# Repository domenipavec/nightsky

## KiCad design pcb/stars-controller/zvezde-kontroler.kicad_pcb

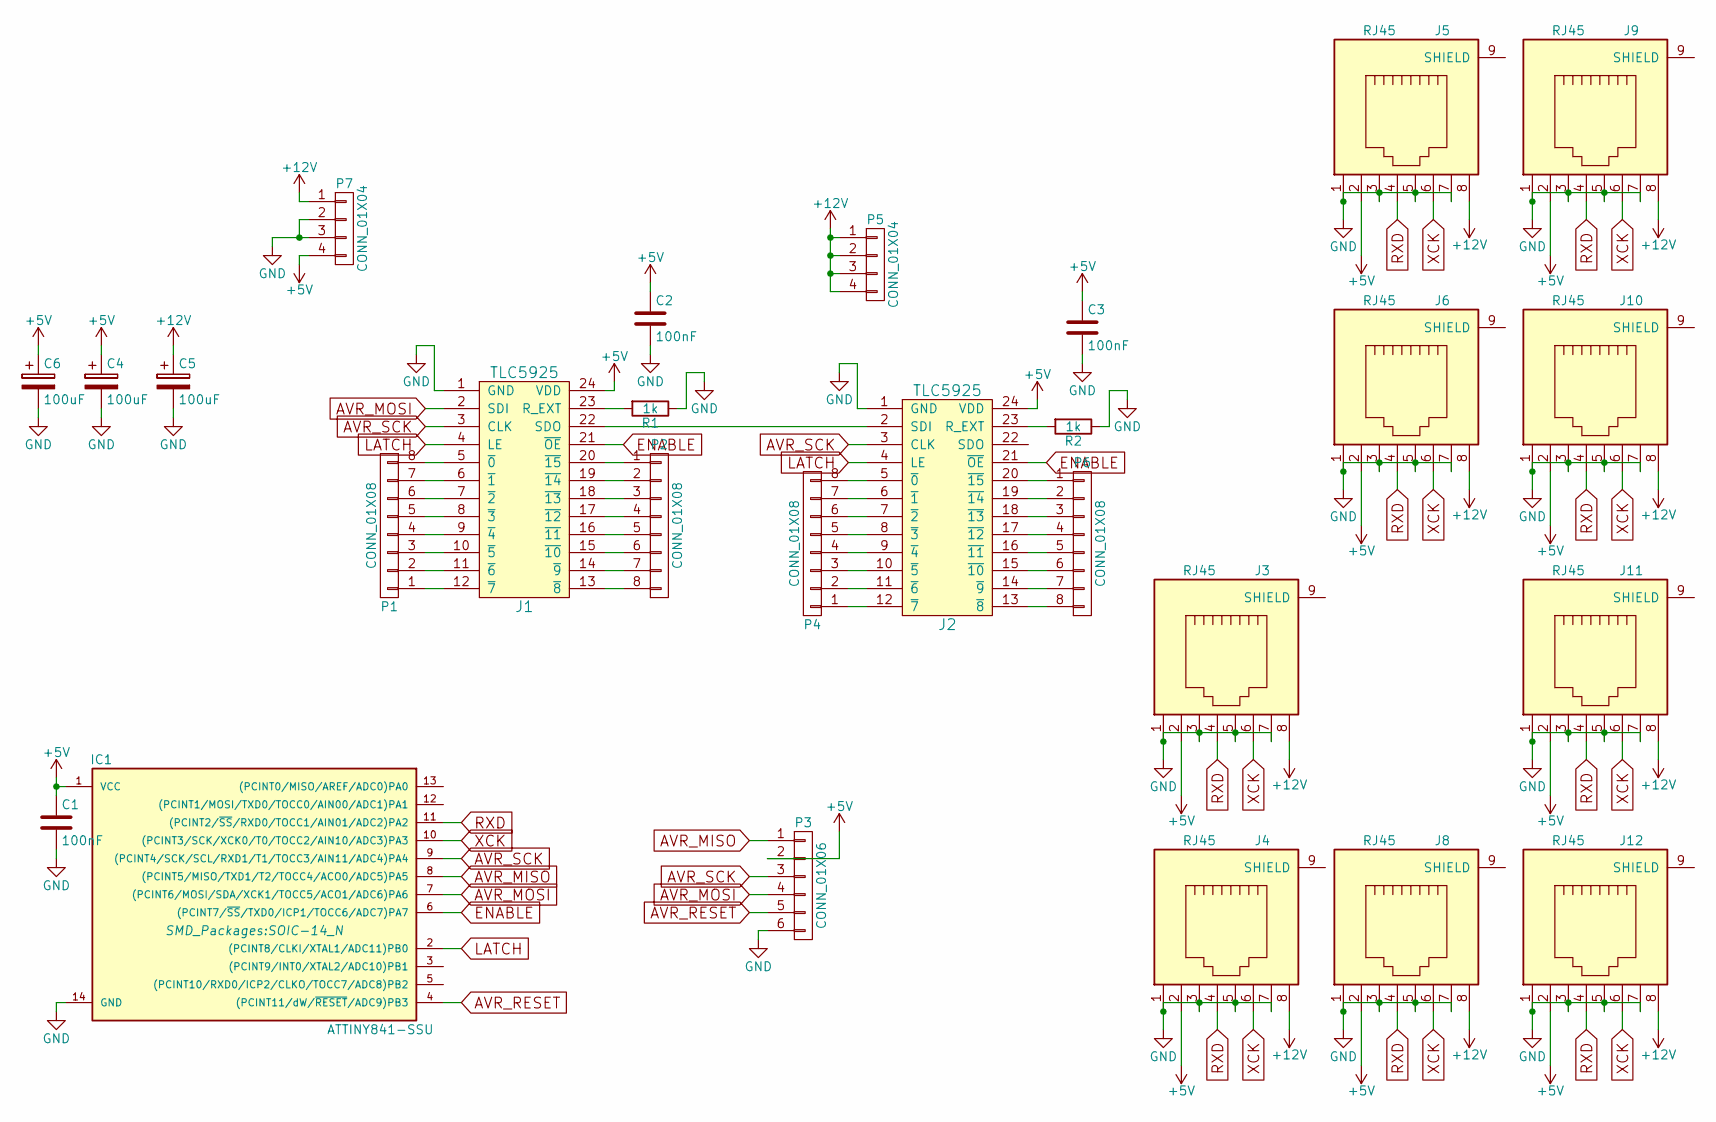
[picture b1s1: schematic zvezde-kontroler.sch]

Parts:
C1, C2, C3: 100nF; C_0603_HandSoldering
C4, C5, C6: 100uF; C_Radial_D6.3_L11.2_P2.5
IC1: ATTINY841-SSU; SOIC-14_N
J1, J2: TLC5925; SOIC-24W_7.5x15.4mm_Pitch1.27mm
J3, J4, J5, J6, J8, J9, J10, J11, J12: RJ45
P1, P2, P4, P6: CONN_01X08; Socket_Strip_Straight_1x08
P3: CONN_01X06; Pin_Header_Straight_2x03_Pitch2.54mm
P5: CONN_01X04; Socket_Strip_Straight_1x04
P7: CONN_01X04; molex
R1, R2: 1k; R_0805_HandSoldering

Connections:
+5V: C1.1, C2.1, C3.1, C4.1, C6.1, IC1.1 (VCC), J1.24 (VDD), J2.24 (VDD), J3.2, J4.2, J5.2, J6.2, J8.2, J9.2, J10.2, J11.2, J12.2, P3.2, P7.4
+12V: C5.1, J3.8, J4.8, J5.8, J6.8, J8.8, J9.8, J10.8, J11.8, J12.8, P5.1, P5.2, P5.3, P5.4, P7.1
AVR_MISO: IC1.8 ((PCINT5/MISO/TXD1/T2/TOCC4/ACO0/ADC5)PA5), P3.1
AVR_MOSI: IC1.7 ((PCINT6/MOSI/SDA/XCK1/TOCC5/ACO1/ADC6)P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), J1.2 (SDI), P3.4
AVR_RESET: IC1.4 ((PCINT11/dW/~RESET~/ADC9)PB3), P3.5
AVR_SCK: IC1.9 ((PCINT4/SCK/SCL/RXD1/T1/TOCC3/AIN11/ADC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), J1.3 (CLK), J2.3 (CLK), P3.3
ENABLE: IC1.6 ((PCINT7/~SS~/TXD0/ICP1/TOCC6/ADC7)PA7), J1.21 (~OE), J2.21 (~OE)
GND: C1.2, C2.2, C3.2, C4.2, C5.2, C6.2, IC1.14 (GND), J1.1 (GND), J2.1 (GND), J3.1, J3.3, J3.5, J3.7, J4.1, J4.3, J4.5, J4.7, J5.1, J5.3, J5.5, J5.7, J6.1, J6.3, J6.5, J6.7, J8.1, J8.3, J8.5, J8.7, J9.1, J9.3, J9.5, J9.7, J10.1, J10.3, J10.5, J10.7, J11.1, J11.3, J11.5, J11.7, J12.1, J12.3, J12.5, J12.7, P3.6, P7.2, P7.3, R1.1, R2.1
LATCH: IC1.2 ((PCINT8/CLKI/XTAL1/ADC11)PB0), J1.4 (LE), J2.4 (LE)
unnamed: J1.5 (~0), P1.8
unnamed: J1.6 (~1), P1.7
unnamed: J1.7 (~2), P1.6
unnamed: J1.8 (~3), P1.5
unnamed: J1.9 (~4), P1.4
unnamed: J1.10 (~5), P1.3
unnamed: J1.11 (~6), P1.2
unnamed: J1.12 (~7), P1.1
unnamed: J1.13 (~8), P2.8
unnamed: J1.14 (~9), P2.7
unnamed: J1.15 (~10), P2.6
unnamed: J1.16 (~11), P2.5
unnamed: J1.17 (~12), P2.4
unnamed: J1.18 (~13), P2.3
unnamed: J1.19 (~14), P2.2
unnamed: J1.20 (~15), P2.1
unnamed: J1.22 (SDO), J2.2 (SDI)
unnamed: J1.23 (R_EXT), R1.2
unnamed: J2.5 (~0), P4.8
unnamed: J2.6 (~1), P4.7
unnamed: J2.7 (~2), P4.6
unnamed: J2.8 (~3), P4.5
unnamed: J2.9 (~4), P4.4
unnamed: J2.10 (~5), P4.3
unnamed: J2.11 (~6), P4.2
unnamed: J2.12 (~7), P4.1
unnamed: J2.13 (~8), P6.8
unnamed: J2.14 (~9), P6.7
unnamed: J2.15 (~10), P6.6
unnamed: J2.16 (~11), P6.5
unnamed: J2.17 (~12), P6.4
unnamed: J2.18 (~13), P6.3
unnamed: J2.19 (~14), P6.2
unnamed: J2.20 (~15), P6.1
unnamed: J2.23 (R_EXT), R2.2
RXD: IC1.11 ((PCINT2/~SS~/RXD0/TOCC1/AIN01/ADC2)PA2), J3.4, J4.4, J5.4, J6.4, J8.4, J9.4, J10.4, J11.4, J12.4
XCK: IC1.10 ((PCINT3/SCK/XCK0/T0/TOCC2/AIN10/ADC3)PA3), J3.6, J4.6, J5.6, J6.6, J8.6, J9.6, J10.6, J11.6, J12.6

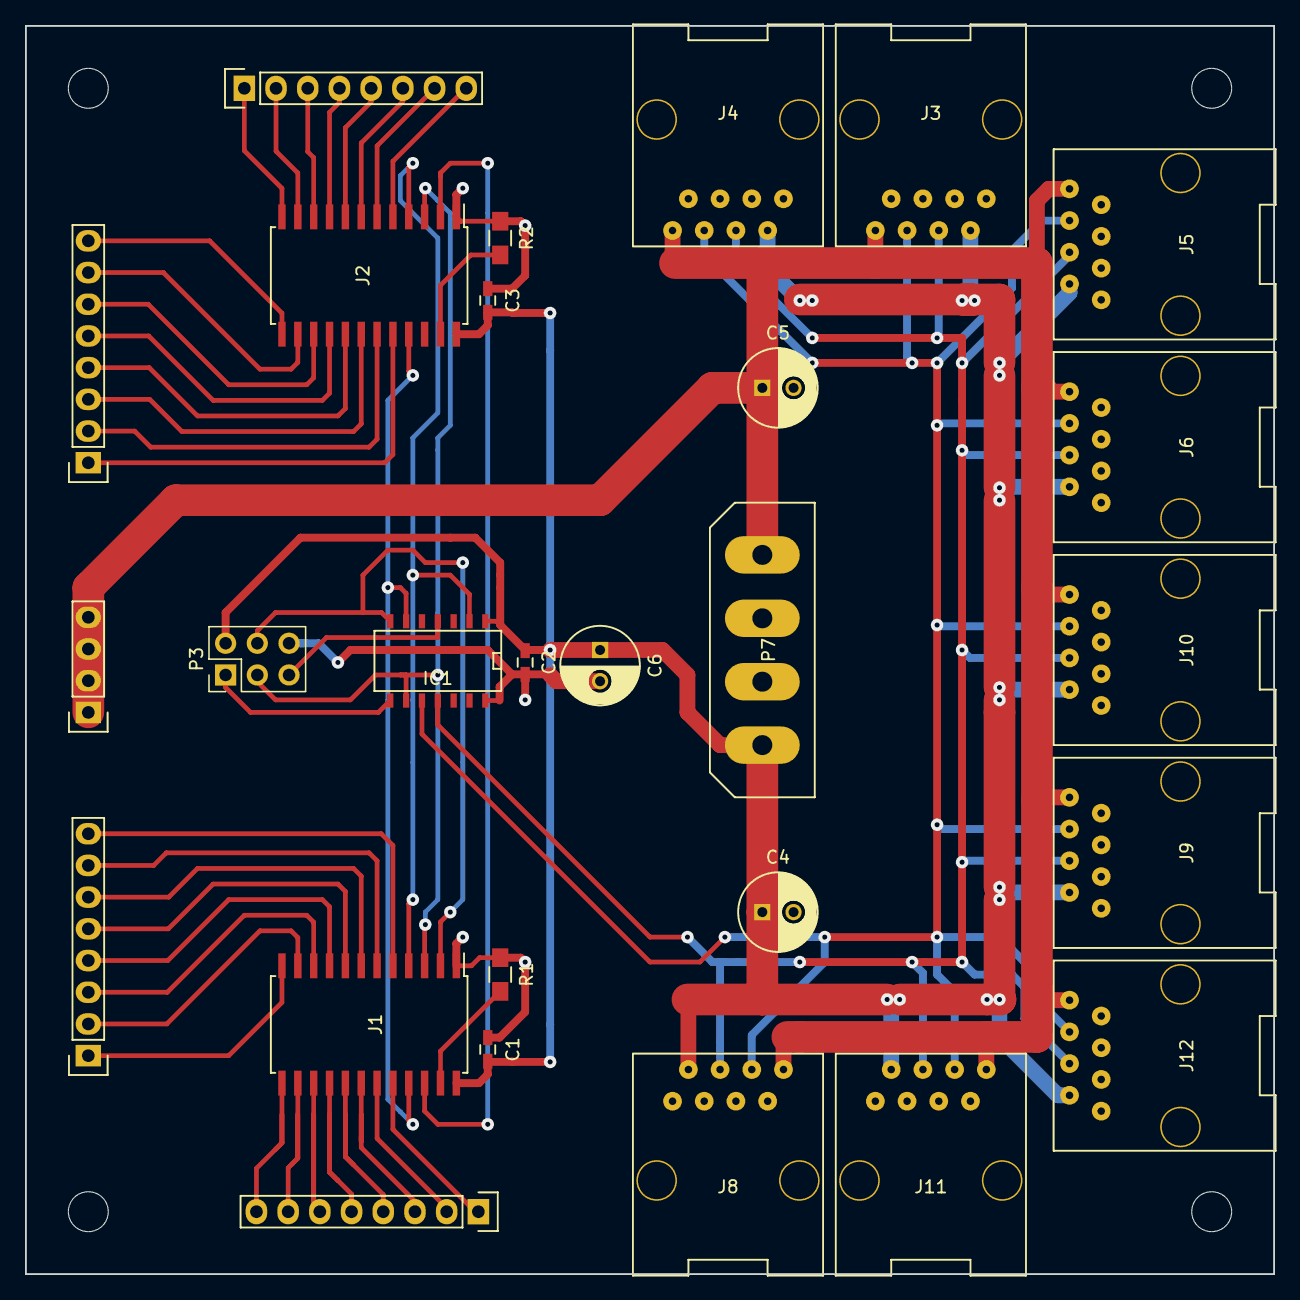
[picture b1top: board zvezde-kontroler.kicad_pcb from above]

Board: 2 copper layers, 100.0 x 100.0 mm, 27 parts (0 on the bottom side), 46 nets.

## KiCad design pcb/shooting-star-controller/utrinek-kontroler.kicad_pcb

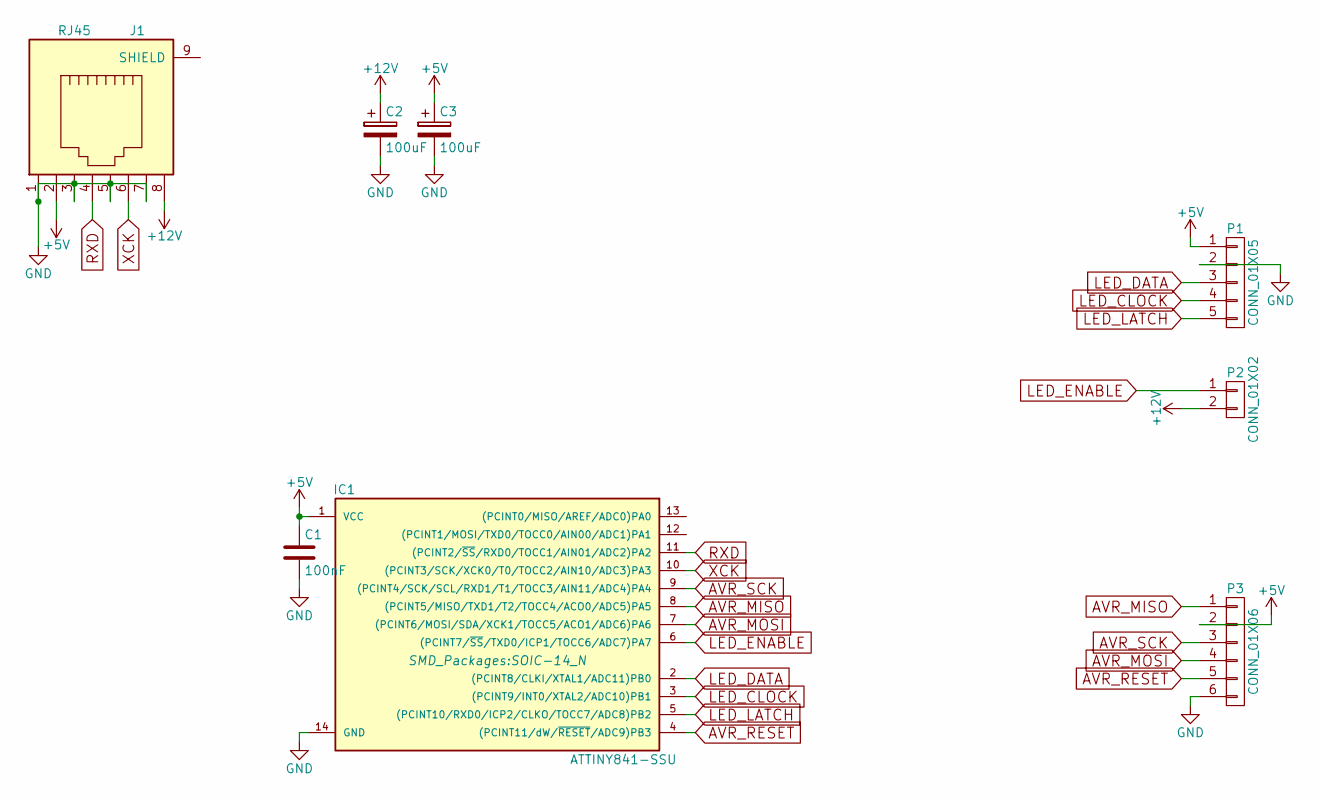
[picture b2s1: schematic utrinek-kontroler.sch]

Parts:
C1: 100nF; C_0603_HandSoldering
C2, C3: 100uF; C_Radial_D8_L11.5_P3.5
IC1: ATTINY841-SSU; SOIC-14_N
J1: RJ45
P1: CONN_01X05; Pin_Header_Straight_1x05
P2: CONN_01X02; Pin_Header_Straight_1x02
P3: CONN_01X06; Pin_Header_Straight_2x03_Pitch2.54mm

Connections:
+5V: C1.1, C3.1, IC1.1 (VCC), J1.2, P1.1, P3.2
+12V: C2.1, J1.8, P2.2
AVR_MISO: IC1.8 ((PCINT5/MISO/TXD1/T2/TOCC4/ACO0/ADC5)PA5), P3.1
AVR_MOSI: IC1.7 ((PCINT6/MOSI/SDA/XCK1/TOCC5/ACO1/ADC6)P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), P3.4
AVR_RESET: IC1.4 ((PCINT11/dW/~RESET~/ADC9)PB3), P3.5
AVR_SCK: IC1.9 ((PCINT4/SCK/SCL/RXD1/T1/TOCC3/AIN11/ADC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), P3.3
GND: C1.2, C2.2, C3.2, IC1.14 (GND), J1.1, J1.3, J1.5, J1.7, P1.2, P3.6
LED_CLOCK: IC1.3 ((PCINT9/INT0/XTAL2/ADC10)PB1), P1.4
LED_DATA: IC1.2 ((PCINT8/CLKI/XTAL1/ADC11)PB0), P1.3
LED_ENABLE: IC1.6 ((PCINT7/~SS~/TXD0/ICP1/TOCC6/ADC7)PA7), P2.1
LED_LATCH: IC1.5 ((PCINT10/RXD0/ICP2/CLKO/TOCC7/ADC8)PB2), P1.5
RXD: IC1.11 ((PCINT2/~SS~/RXD0/TOCC1/AIN01/ADC2)PA2), J1.4
XCK: IC1.10 ((PCINT3/SCK/XCK0/T0/TOCC2/AIN10/ADC3)PA3), J1.6

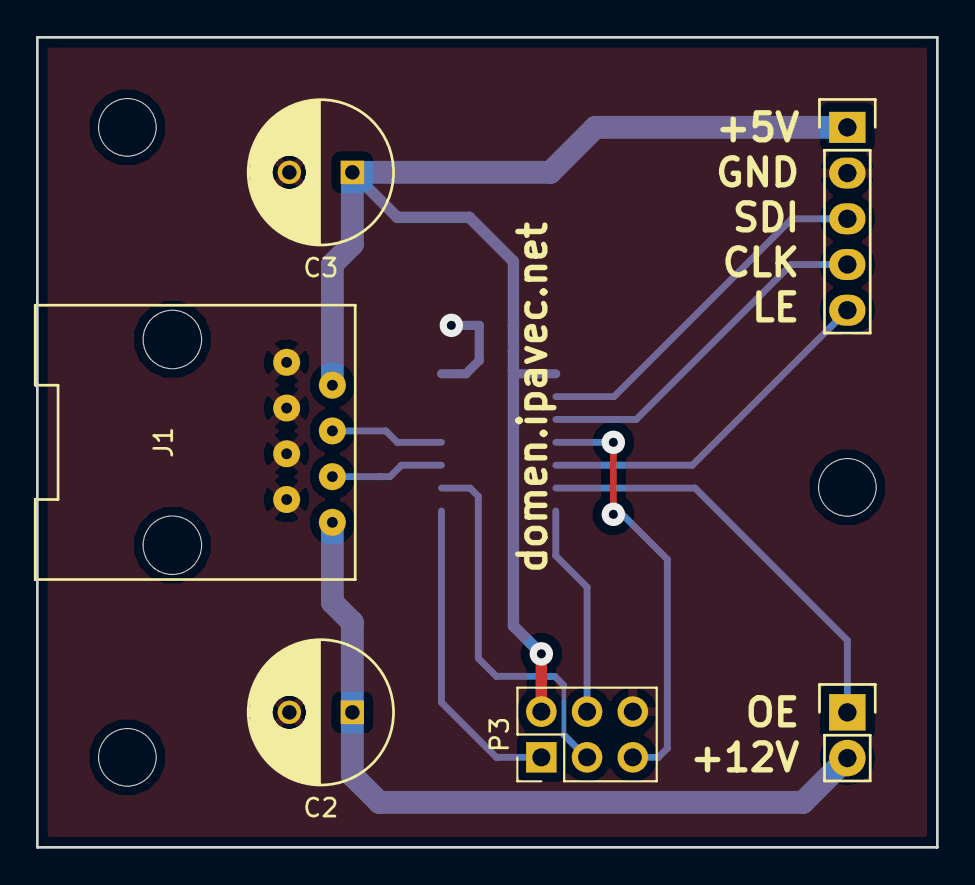
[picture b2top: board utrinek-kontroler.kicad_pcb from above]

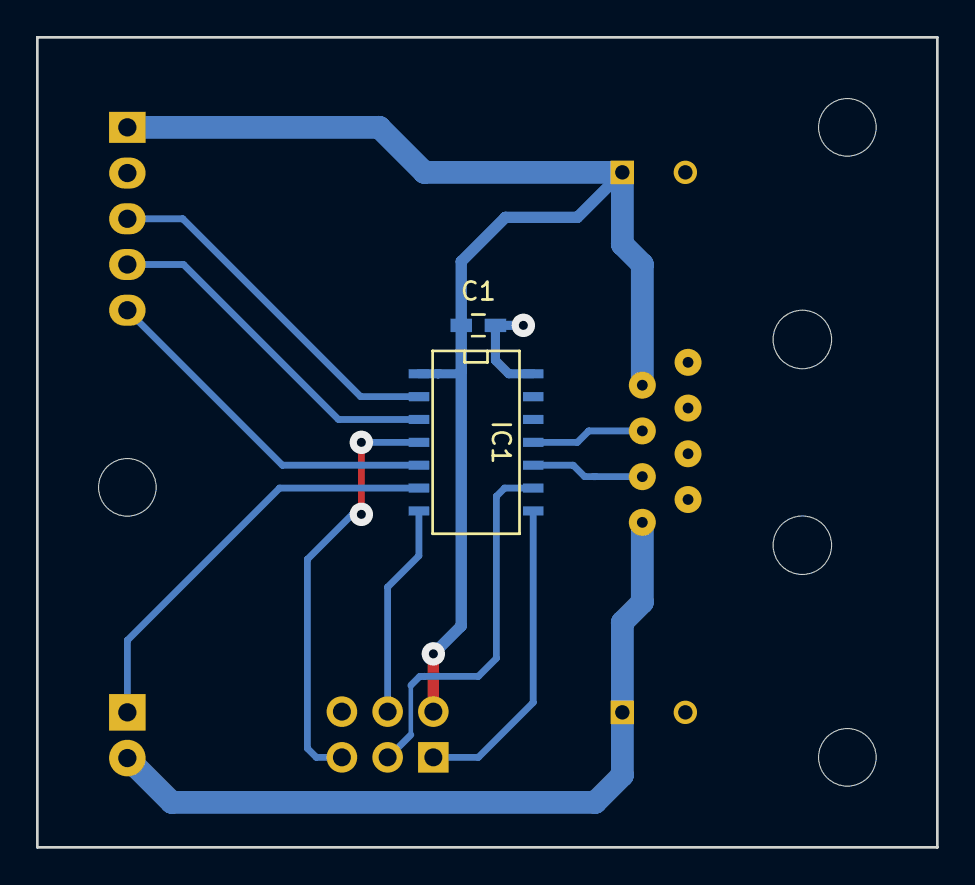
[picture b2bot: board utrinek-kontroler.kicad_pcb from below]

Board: 2 copper layers, 50.0 x 45.0 mm, 8 parts (2 on the bottom side), 13 nets.

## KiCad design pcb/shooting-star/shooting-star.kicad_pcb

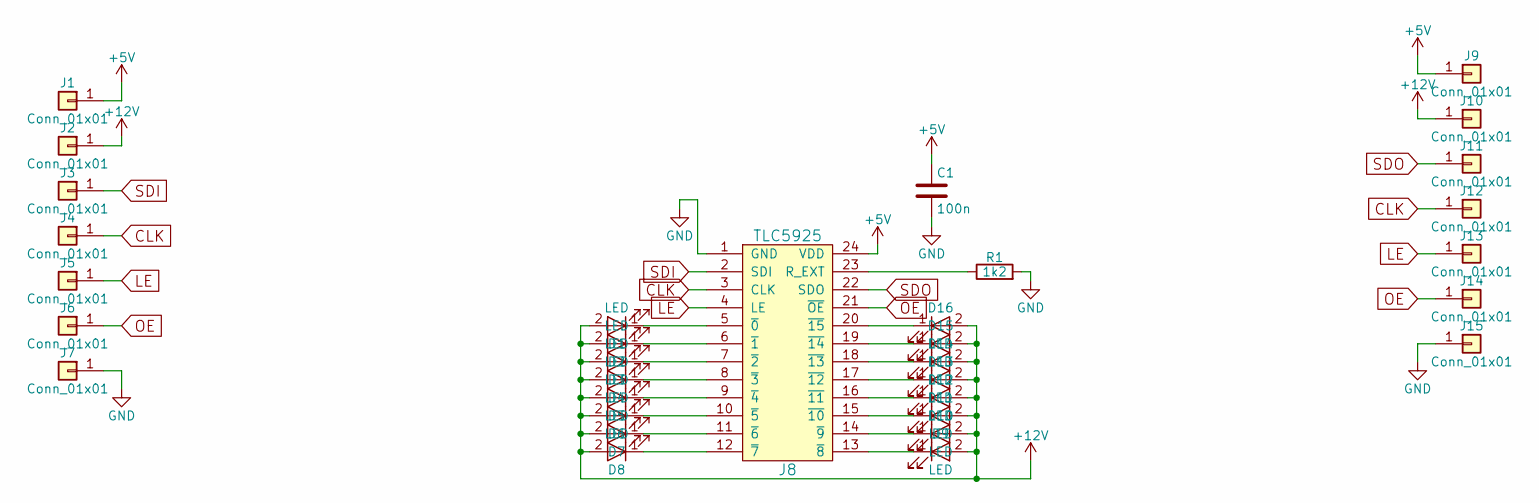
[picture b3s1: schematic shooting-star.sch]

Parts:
C1: 100n; C_0603_HandSoldering
D1, D2, D3, D4, D5, D6, D7, D8, D9, D10, D11, D12, D13, D14, D15, D16: LED; LED_D5.0mm
J1, J2, J3, J4, J5, J6, J7, J9, J10, J11, J12, J13, J14, J15: Conn_01x01; Wire_pad_2.5mm_1.25mm
J8: TLC5925; SOIC-24W_7.5x15.4mm_Pitch1.27mm
R1: 1k2; R_0805_HandSoldering

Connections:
+5V: C1.1, J1.1, J8.24 (VDD), J9.1
+12V: D1.2 (A), D2.2 (A), D3.2 (A), D4.2 (A), D5.2 (A), D6.2 (A), D7.2 (A), D8.2 (A), D9.2 (A), D10.2 (A), D11.2 (A), D12.2 (A), D13.2 (A), D14.2 (A), D15.2 (A), D16.2 (A), J2.1, J10.1
CLK: J4.1, J8.3 (CLK), J12.1
GND: C1.2, J7.1, J8.1 (GND), J15.1, R1.2
LE: J5.1, J8.4 (LE), J13.1
unnamed: D1.1 (K), J8.5 (~0)
unnamed: D2.1 (K), J8.6 (~1)
unnamed: D3.1 (K), J8.7 (~2)
unnamed: D4.1 (K), J8.8 (~3)
unnamed: D5.1 (K), J8.9 (~4)
unnamed: D6.1 (K), J8.10 (~5)
unnamed: D7.1 (K), J8.11 (~6)
unnamed: D8.1 (K), J8.12 (~7)
unnamed: D9.1 (K), J8.13 (~8)
unnamed: D10.1 (K), J8.14 (~9)
unnamed: D11.1 (K), J8.15 (~10)
unnamed: D12.1 (K), J8.16 (~11)
unnamed: D13.1 (K), J8.17 (~12)
unnamed: D14.1 (K), J8.18 (~13)
unnamed: D15.1 (K), J8.19 (~14)
unnamed: D16.1 (K), J8.20 (~15)
unnamed: J8.23 (R_EXT), R1.1
OE: J6.1, J8.21 (~OE), J14.1
SDI: J3.1, J8.2 (SDI)
SDO: J8.22 (SDO), J11.1

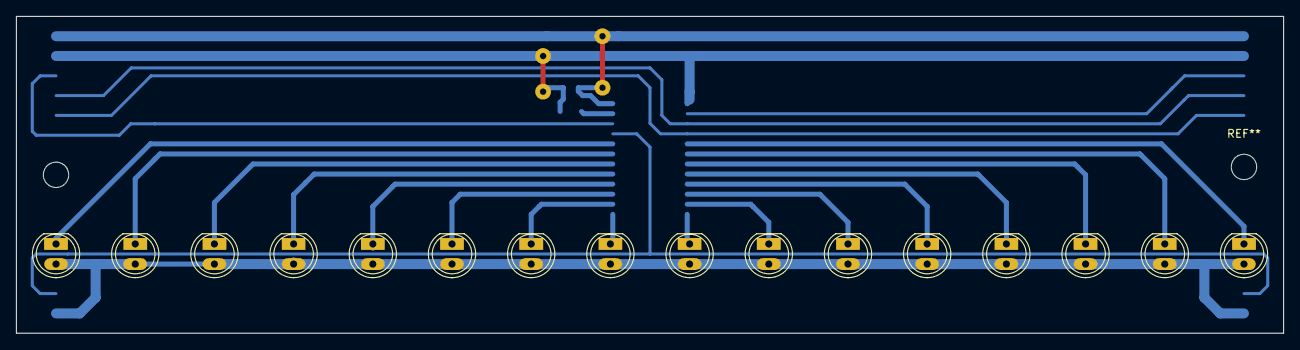
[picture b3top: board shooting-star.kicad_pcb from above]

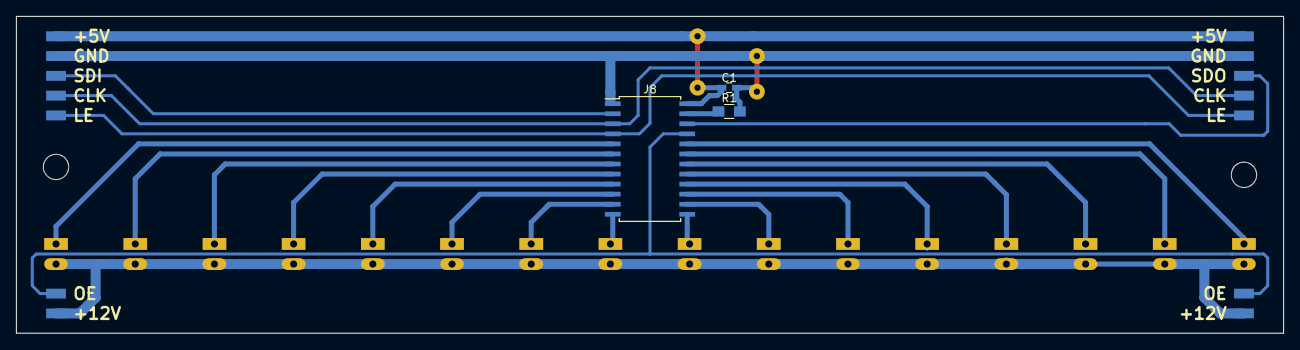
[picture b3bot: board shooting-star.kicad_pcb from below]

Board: 2 copper layers, 160.0 x 40.0 mm, 33 parts (17 on the bottom side), 25 nets.

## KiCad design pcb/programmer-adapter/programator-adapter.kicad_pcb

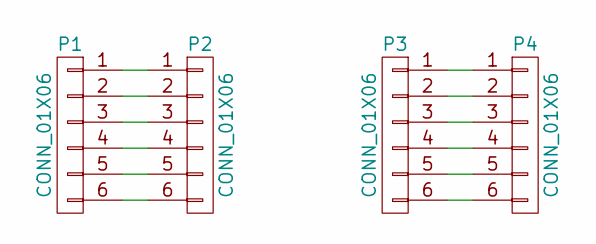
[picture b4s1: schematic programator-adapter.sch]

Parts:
P1, P3: CONN_01X06; Pin_Header_Straight_1x06
P2, P4: CONN_01X06; ATTINY841-SPI

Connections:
unnamed: P1.1, P2.1
unnamed: P1.2, P2.2
unnamed: P1.3, P2.3
unnamed: P1.4, P2.4
unnamed: P1.5, P2.5
unnamed: P1.6, P2.6
unnamed: P3.1, P4.1
unnamed: P3.2, P4.2
unnamed: P3.3, P4.3
unnamed: P3.4, P4.4
unnamed: P3.5, P4.5
unnamed: P3.6, P4.6

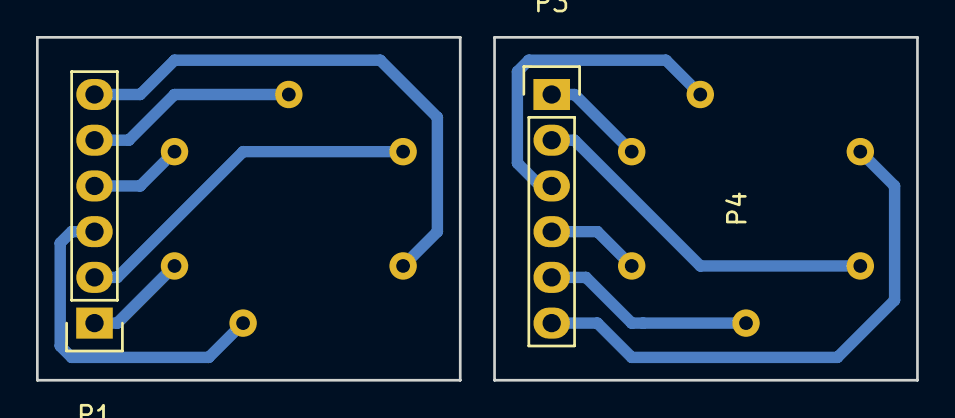
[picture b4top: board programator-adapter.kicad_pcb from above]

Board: 2 copper layers, 48.9 x 19.1 mm, 4 parts (1 on the bottom side), 12 nets.

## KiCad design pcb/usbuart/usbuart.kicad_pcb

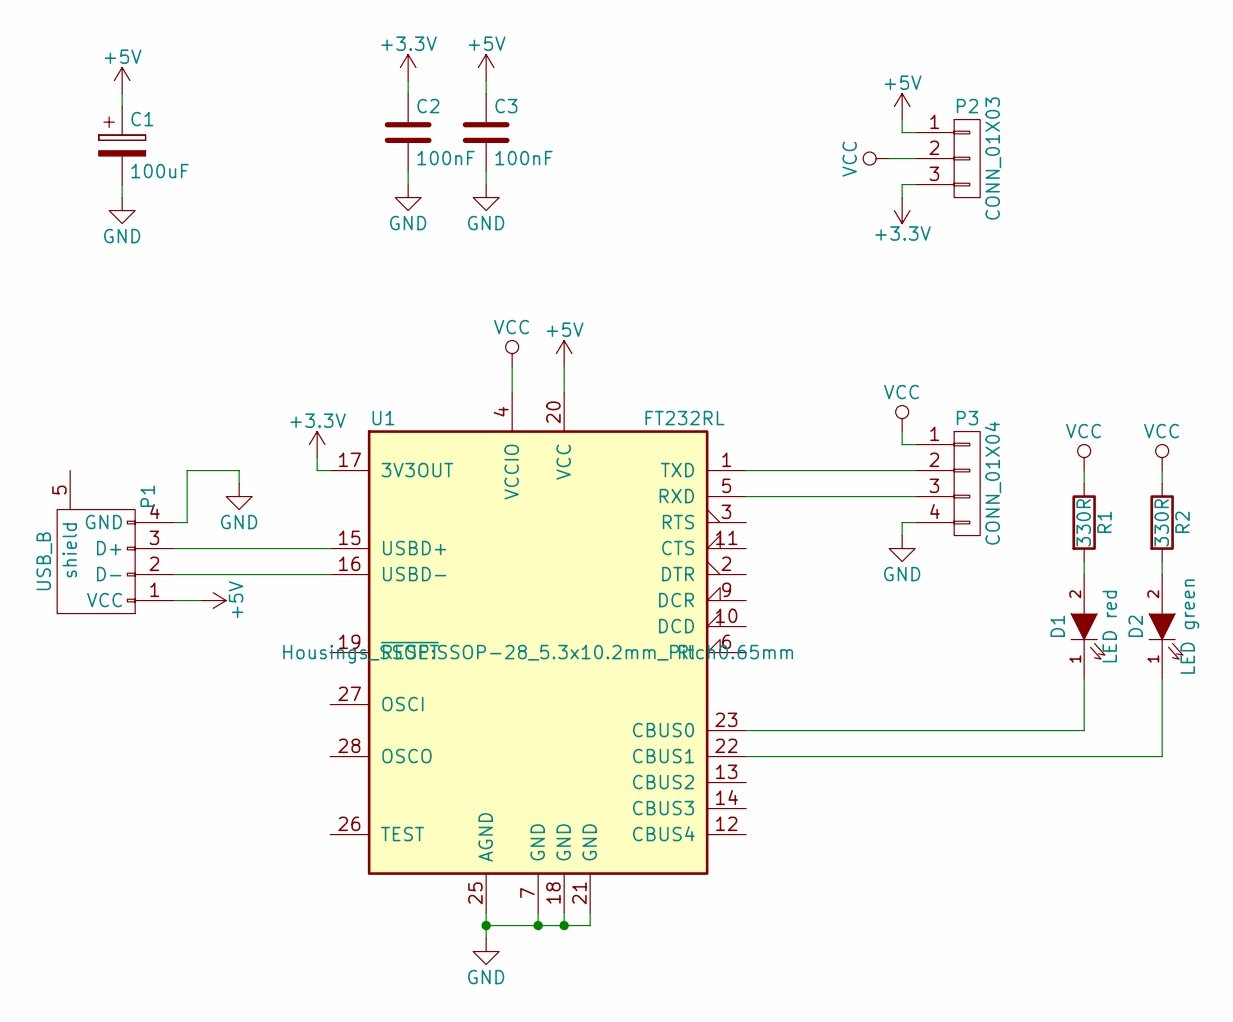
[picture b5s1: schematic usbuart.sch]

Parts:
C1: 100uF; C_Radial_D6.3_L11.2_P2.5
C2, C3: 100nF; C_0603_HandSoldering
D1: LED red; LED-3MM
D2: LED green; LED-3MM
P1: USB_B
P2: CONN_01X03; Pin_Header_Straight_1x03
P3: CONN_01X04; Pin_Header_Straight_1x04
R1, R2: 330R; R_0805_HandSoldering
U1: FT232RL; SSOP-28_5.3x10.2mm_Pitch0.65mm

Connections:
+3V3: C2.1, P2.3, U1.17 (3V3OUT)
+5V: C1.1, C3.1, P1.1 (VCC), P2.1, U1.20 (VCC)
GND: C1.2, C2.2, C3.2, P1.4 (GND), P3.4, U1.7 (GND), U1.18 (GND), U1.21 (GND), U1.25 (AGND)
unnamed: D1.1 (K), U1.23 (CBUS0)
unnamed: D1.2 (A), R1.2
unnamed: D2.1 (K), U1.22 (CBUS1)
unnamed: D2.2 (A), R2.2
unnamed: P1.2 (D-), U1.16 (USBD-)
unnamed: P1.3 (D+), U1.15 (USBD+)
unnamed: P3.2, U1.1 (TXD)
unnamed: P3.3, U1.5 (RXD)
VCC: P2.2, P3.1, R1.1, R2.1, U1.4 (VCCIO)

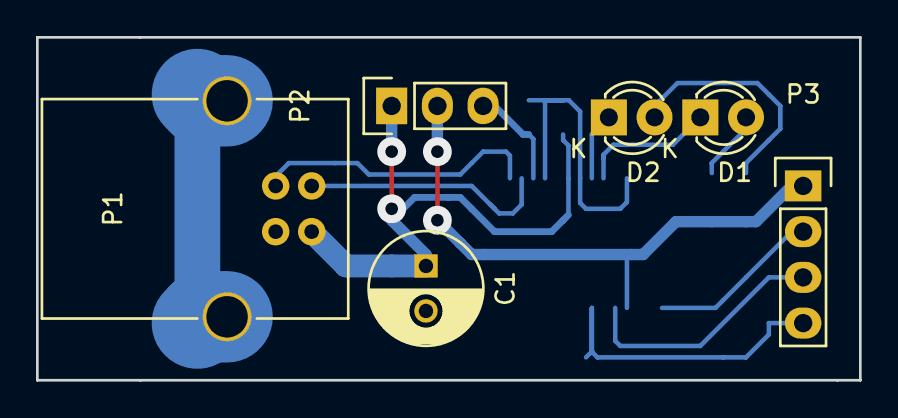
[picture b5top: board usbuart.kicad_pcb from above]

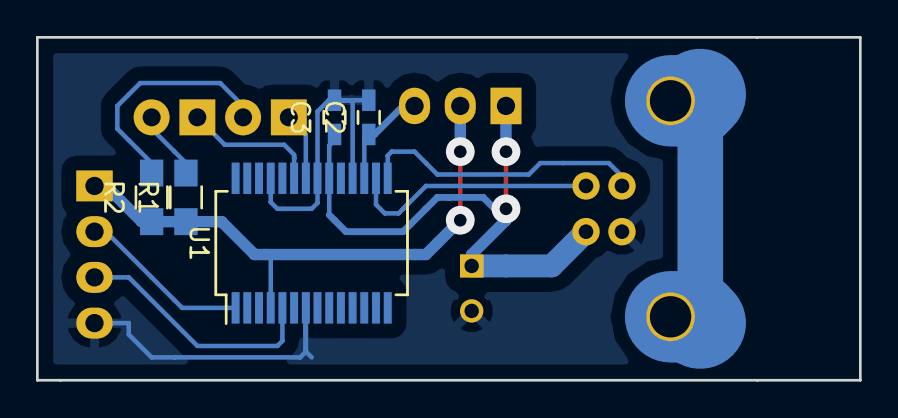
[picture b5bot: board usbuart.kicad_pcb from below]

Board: 2 copper layers, 45.7 x 19.0 mm, 11 parts (5 on the bottom side), 12 nets.

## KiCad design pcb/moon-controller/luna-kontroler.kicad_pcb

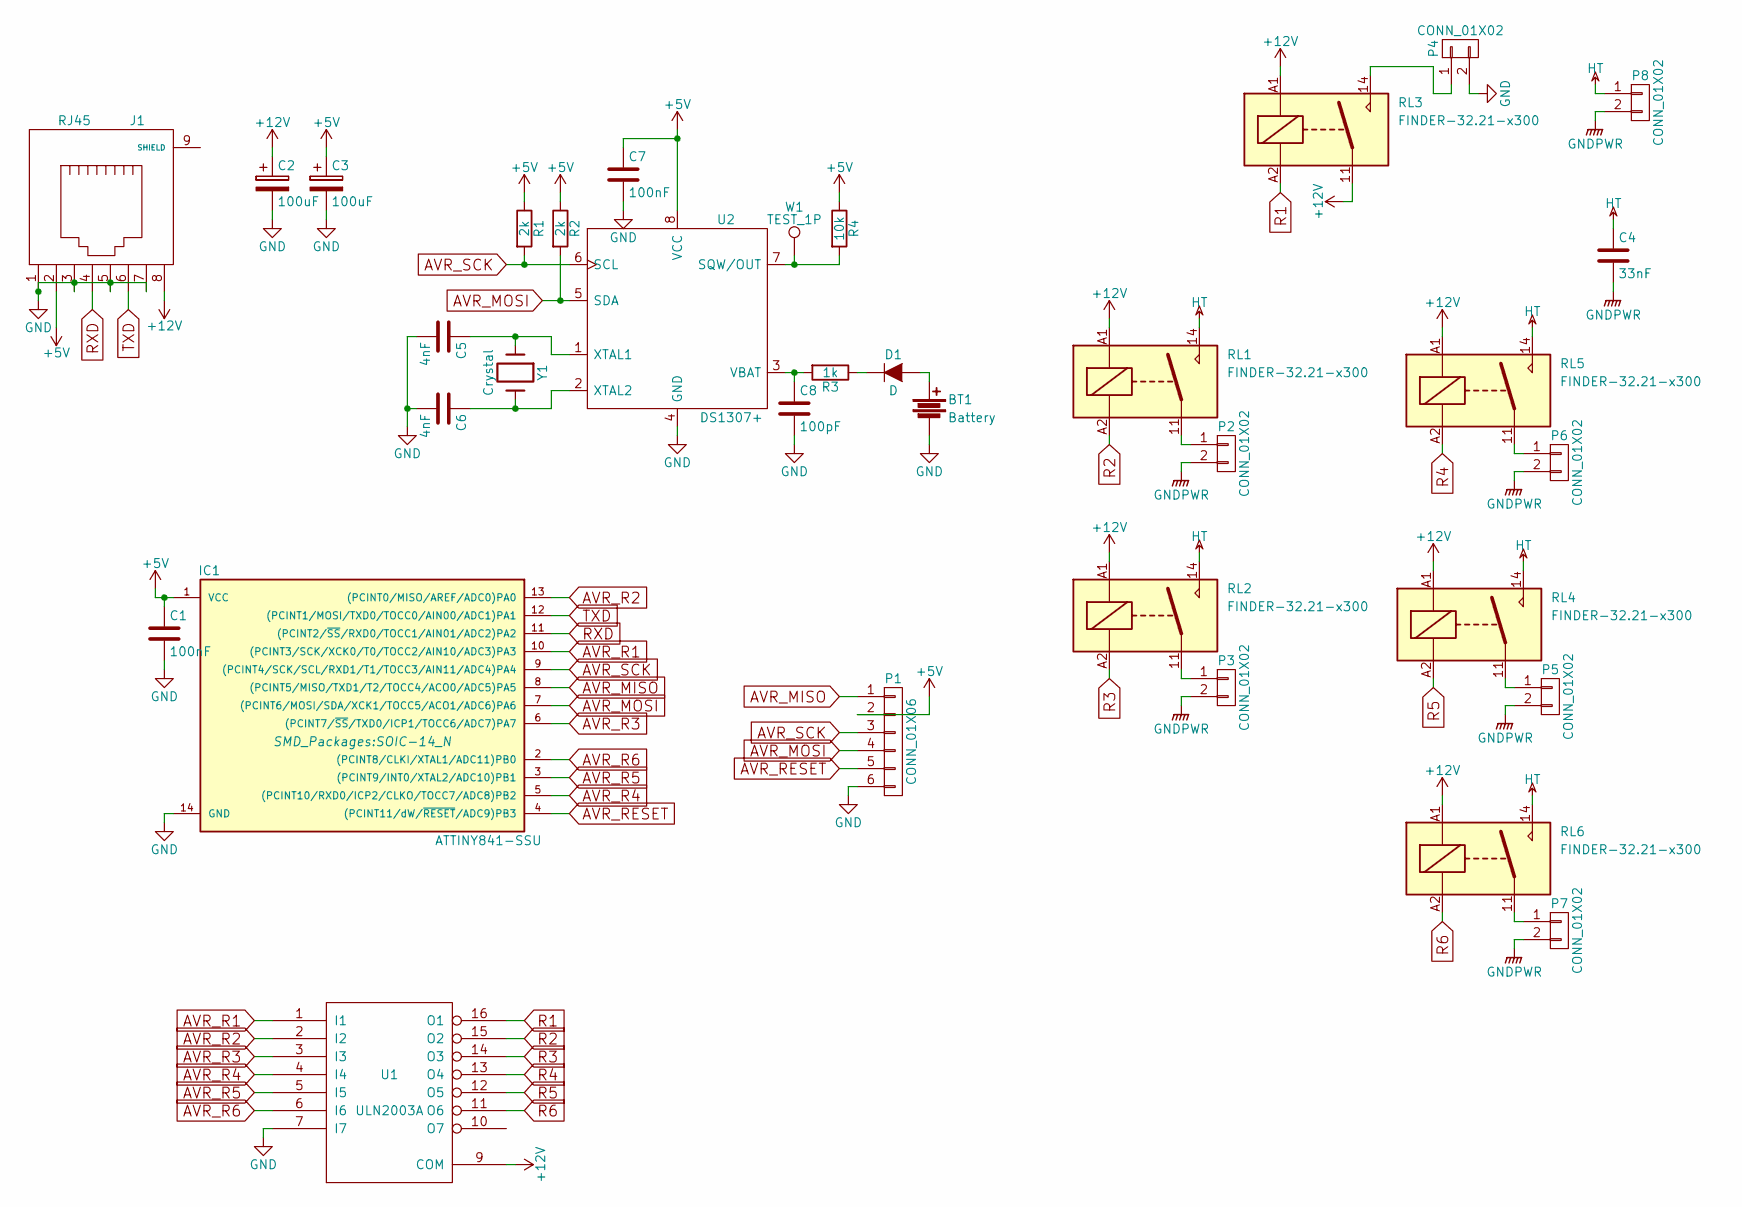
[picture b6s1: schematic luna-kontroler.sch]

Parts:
BT1: Battery; cr2032holder
C1, C7: 100nF; C_0603_HandSoldering
C2, C3: 100uF; C_Radial_D6.3_L11.2_P2.5
C4: 33nF; C_Rect_L13_W4_P10
C5, C6: 4nF; C_0805_HandSoldering
C8: 100pF; C_0805_HandSoldering
D1: D; R_0805_HandSoldering
IC1: ATTINY841-SSU; SOIC-14_N
J1: RJ45
P1: CONN_01X06; ATTINY841-SPI
P2, P3, P4, P5, P6, P7, P8: CONN_01X02; TerminalBlock_Pheonix_MKDS1.5-2pol
R1, R2: 2k; R_0805_HandSoldering
R3: 1k; R_0805_HandSoldering
R4: 10k; R_0805_HandSoldering
RL1, RL2, RL3, RL4, RL5, RL6: FINDER-32.21-x300; relay
U1: ULN2003A; SOIC-16_3.9x9.9mm_Pitch1.27mm
U2: DS1307+; SOIC-8_3.9x4.9mm_Pitch1.27mm
W1: TEST_1P; Measurement_Point_Round-SMD-Pad_Small
Y1: Crystal; Crystal_Round_Horizontal_2mm

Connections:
+5V: C1.1, C3.1, C7.1, IC1.1 (VCC), J1.2, P1.2, R1.1, R2.1, R4.1, U2.8 (VCC)
+12V: C2.1, J1.8, RL1.A1, RL2.A1, RL3.11, RL3.A1, RL4.A1, RL5.A1, RL6.A1, U1.9 (COM)
AVR_MISO: IC1.8 ((PCINT5/MISO/TXD1/T2/TOCC4/ACO0/ADC5)PA5), P1.1
AVR_MOSI: IC1.7 ((PCINT6/MOSI/SDA/XCK1/TOCC5/ACO1/ADC6)P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), P1.4, R2.2, U2.5 (SDA)
AVR_R1: IC1.10 ((PCINT3/SCK/XCK0/T0/TOCC2/AIN10/ADC3)PA3), U1.1 (I1)
AVR_R2: IC1.13 ((PCINT0/MISO/AREF/ADC0)PA0), U1.2 (I2)
AVR_R3: IC1.6 ((PCINT7/~SS~/TXD0/ICP1/TOCC6/ADC7)PA7), U1.3 (I3)
AVR_R4: IC1.5 ((PCINT10/RXD0/ICP2/CLKO/TOCC7/ADC8)PB2), U1.4 (I4)
AVR_R5: IC1.3 ((PCINT9/INT0/XTAL2/ADC10)PB1), U1.5 (I5)
AVR_R6: IC1.2 ((PCINT8/CLKI/XTAL1/ADC11)PB0), U1.6 (I6)
AVR_RESET: IC1.4 ((PCINT11/dW/~RESET~/ADC9)PB3), P1.5
AVR_SCK: IC1.9 ((PCINT4/SCK/SCL/RXD1/T1/TOCC3/AIN11/ADC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), P1.3, R1.2, U2.6 (SCL)
GND: BT1.2, C1.2, C2.2, C3.2, C5.2, C6.2, C7.2, C8.2, IC1.14 (GND), J1.1, J1.3, J1.5, J1.7, P1.6, P4.2, U1.7 (I7), U1.8 (GND), U2.4 (GND)
GNDPWR: C4.2, P2.2, P3.2, P5.2, P6.2, P7.2, P8.2
HT: C4.1, P8.1, RL1.14, RL2.14, RL4.14, RL5.14, RL6.14
unnamed: BT1.1, D1.2 (A)
unnamed: C5.1, U2.1 (XTAL1), Y1.1
unnamed: C6.1, U2.2 (XTAL2), Y1.2
unnamed: C8.1, R3.2, U2.3 (VBAT)
unnamed: D1.1 (K), R3.1
unnamed: P2.1, RL1.11
unnamed: P3.1, RL2.11
unnamed: P4.1, RL3.14
unnamed: P5.1, RL4.11
unnamed: P6.1, RL5.11
unnamed: P7.1, RL6.11
unnamed: R4.2, U2.7 (SQW/OUT), W1.1
R1: RL3.A2, U1.16 (O1)
R2: RL1.A2, U1.15 (O2)
R3: RL2.A2, U1.14 (O3)
R4: RL5.A2, U1.13 (O4)
R5: RL4.A2, U1.12 (O5)
R6: RL6.A2, U1.11 (O6)
RXD: IC1.11 ((PCINT2/~SS~/RXD0/TOCC1/AIN01/ADC2)PA2), J1.4
TXD: IC1.12 ((PCINT1/MOSI/TXD0/TOCC0/AIN00/ADC1)PA1), J1.6

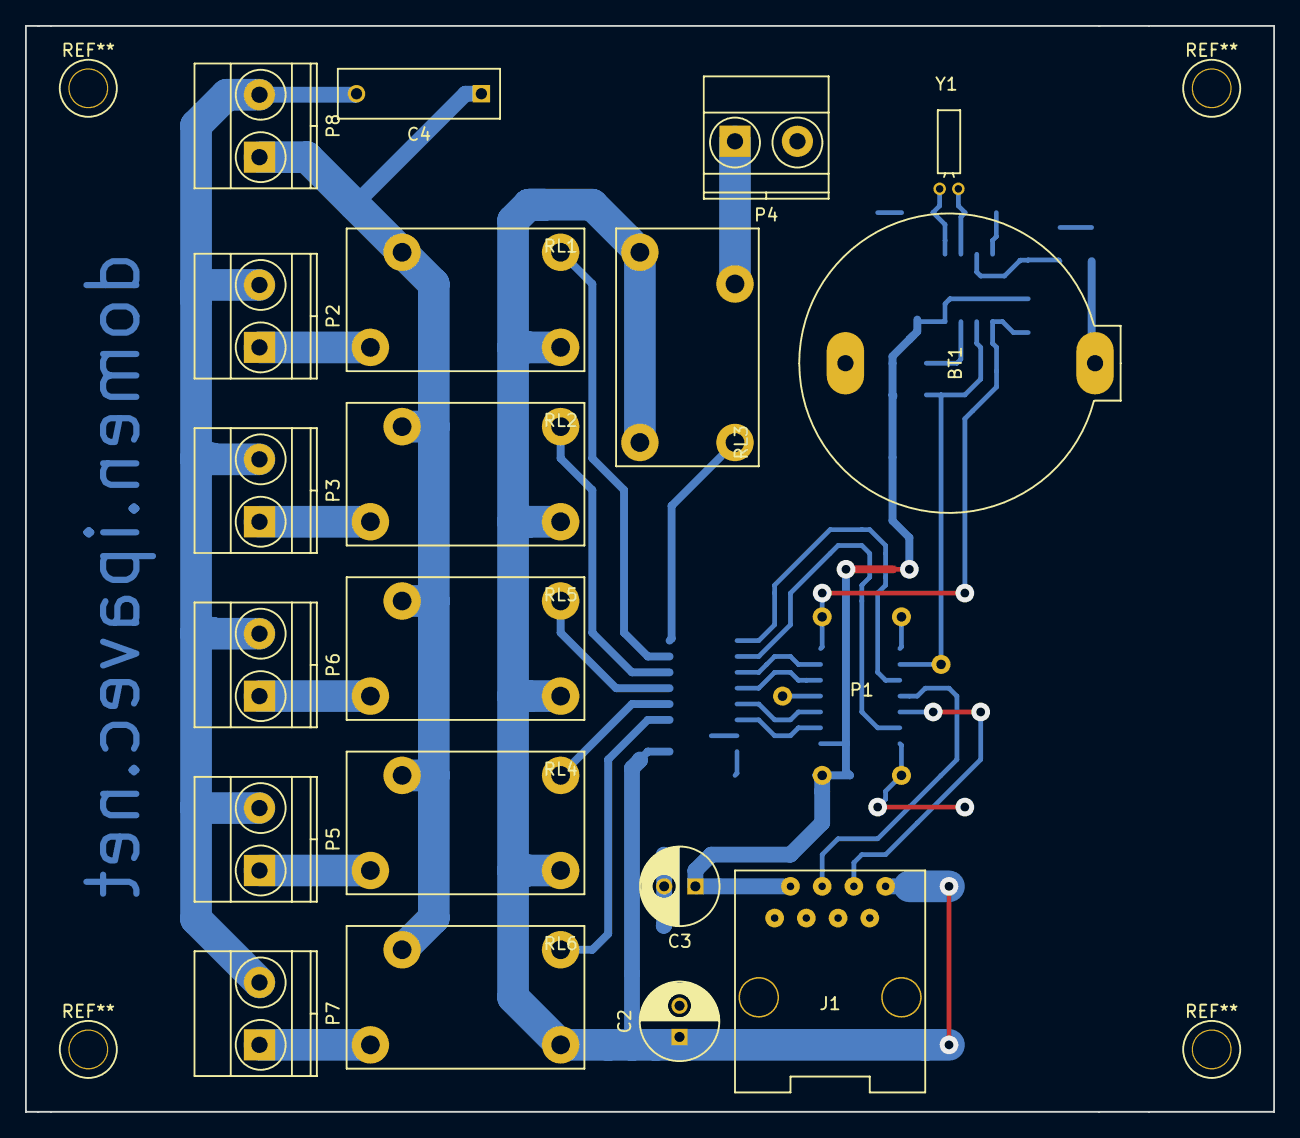
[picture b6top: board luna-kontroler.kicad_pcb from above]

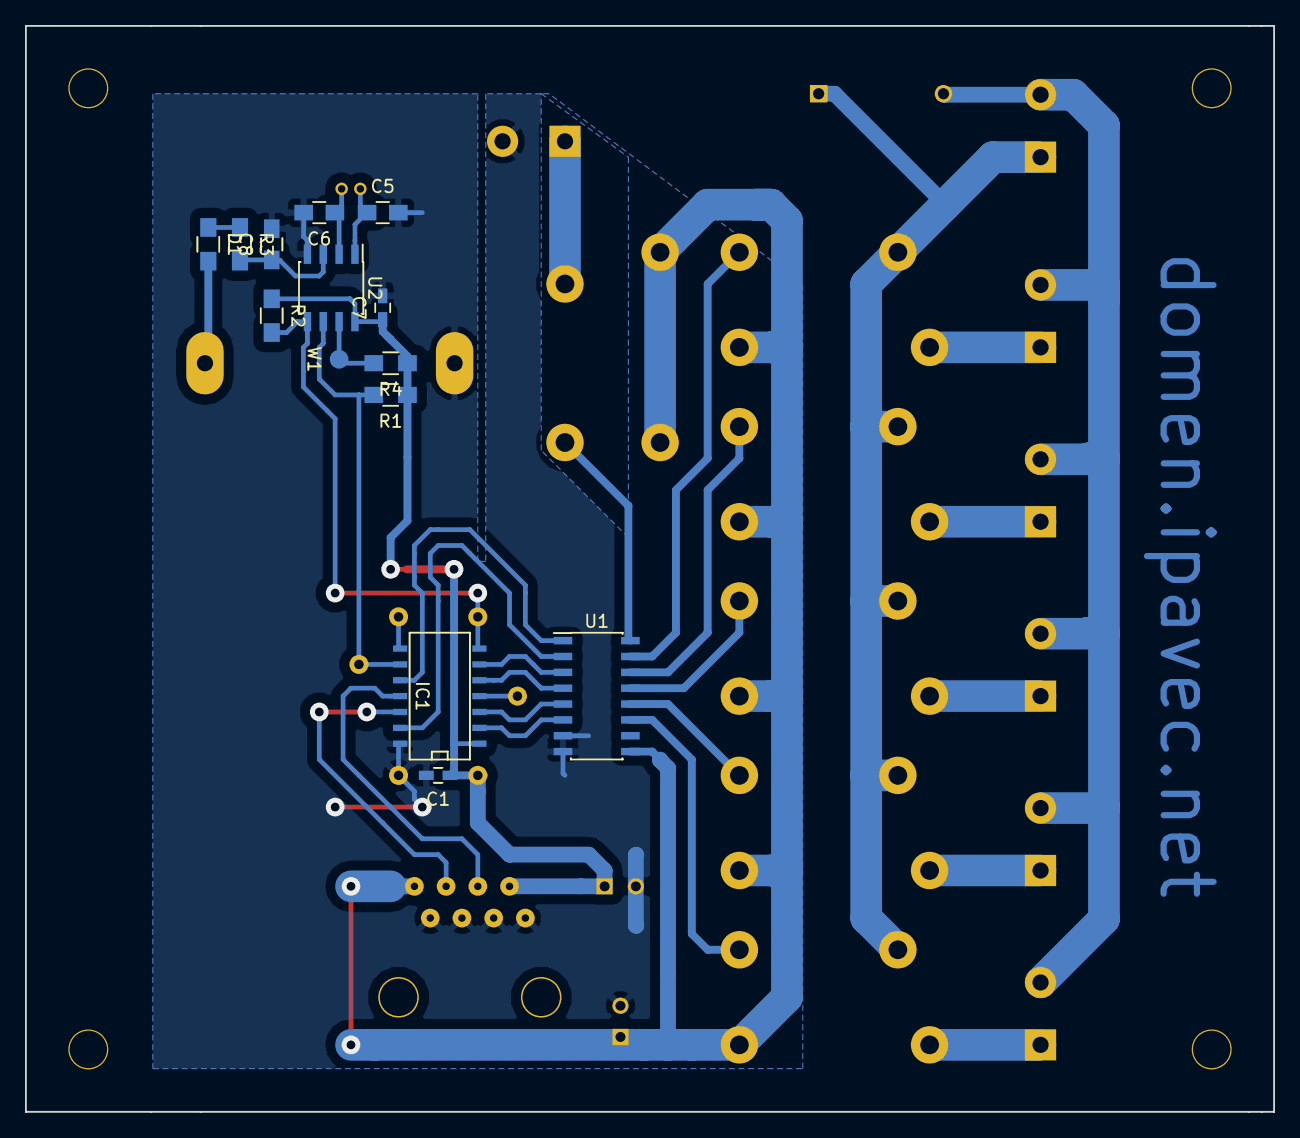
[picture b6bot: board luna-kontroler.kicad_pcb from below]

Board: 2 copper layers, 100.0 x 87.0 mm, 34 parts (14 on the bottom side), 35 nets.

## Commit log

2016-12-08 Inkscape coordinates export
2016-12-08 Stars plan
2016-12-08 Pcbs
2016-12-08 Added firmware
2016-12-08 Added python control script
2017-11-03 Shema david
2017-12-08 Double sided pcbs
2017-12-08 Python control with snow and different star configs
2017-12-08 Stars for 2017
2017-12-08 stars with cloud support
2018-02-05 Added david-2
2019-12-02 Program with fixed brightness values
